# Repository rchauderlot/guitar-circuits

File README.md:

# Guitar Circuits

A place for my guitar-related circuits. 

For the moment, I just made some simple circuits to help me in the process of building guitar effects. But, my plans are add more complex circuits, like pedals, on board effects or, even, full amps, in the future.

All of the circuits in this repo are made using the freeware version of the [EAGLE CAD software](http://www.cadsoftusa.com/), which is cross-platform and has no cost for a hobbyist use. You could download it from the [EAGLE download page](http://www.cadsoftusa.com/download-eagle/)

To configure EAGLE I just add the paths of where the repo is cloned to the project and libraries directories in the *Options* > *Directories* menu. Remember, directories are colon separated in EAGLE. A configuration sample is (it is my current configuration ;-) ):

Libraries:
<pre><code>
$EAGLEDIR/lbr:$HOME/Documents/circuits/guitar-circuits/libs/
</pre></code>

Projects:
<pre><code>
$HOME/Documents/circuits:$EAGLEDIR/projects/examples
</pre></code>

## Circuits

### gm-lbr
This is not a circuit it is a library got form [Gaussmarkov website](http://gaussmarkov.net/) (very cool site, check it out). I’m using it because it is oriented to create pedals and fits my needs very well. It is free, but, all the copyrights belongs to Gaussmarkov as he says in his [About page](http://gaussmarkov.net/wordpress/about/).

### true-bypass
This is a tiny board intended to be attached to a heavy duty foot switch and where you connect all the parts of the circuit (effect board, jacks, led, battery clip and power supply). I made it to avoid to have a mess of wires inside of the pedal case. It is a single sided board, and it is very easy to develop at home.

### true-bypass-2.0
This board is based on the previous one but adds the feature of disconect the power supply when the output jack is unpluged. A stereo jack at the output is needed to take that advantadge.

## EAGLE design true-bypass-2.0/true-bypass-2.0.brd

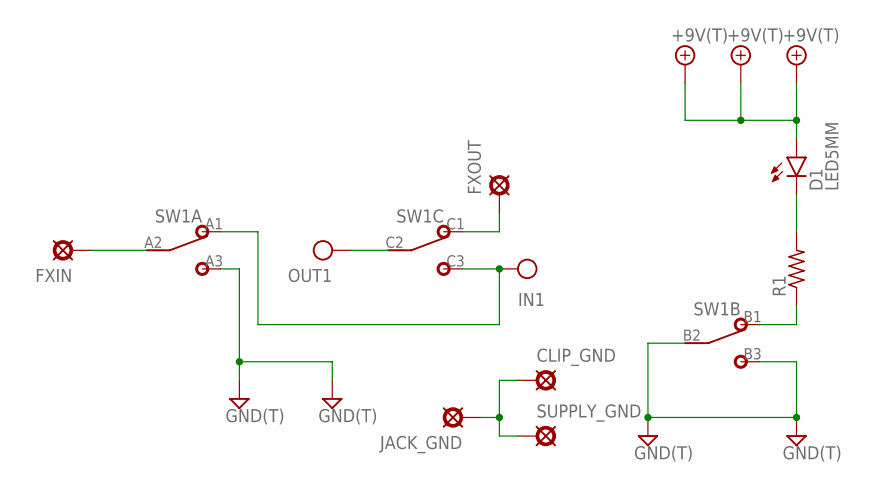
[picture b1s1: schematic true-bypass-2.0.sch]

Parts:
+9V1, +9V2, +9V3: +9V(T); SQUARE
CLIP_GND: PAD; SQUARE
D1: LED5MM
FXIN: PAD; SQUARE
FXOUT: PAD; SQUARE
GND1, GND3, GND4, GND5: GND(T); SQUARE
IN1: IN(T); SQUARE
JACK_GND: PAD; SQUARE
OUT1: OUT(T); SQUARE
R1: 6MM.3; R0207/3
SUPPLY_GND: PAD; SQUARE
SW1: 3PDTBLUE; CHINABLUE

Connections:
+9V: +9V1.1, +9V2.1, +9V3.1, D1.A
GND: GND1.1, GND3.1, GND4.1, GND5.1, SW1.A3 (3), SW1.B2 (2), SW1.B3 (3)
IN: IN1.1, SW1.A1 (1), SW1.C3 (3)
unnamed: FXIN.1, SW1.A2 (2)
unnamed: D1.K (C), R1.2
unnamed: R1.1, SW1.B1 (1)
unnamed: FXOUT.1, SW1.C1 (1)
unnamed: CLIP_GND.1, JACK_GND.1, SUPPLY_GND.1
OUT: OUT1.1, SW1.C2 (2)

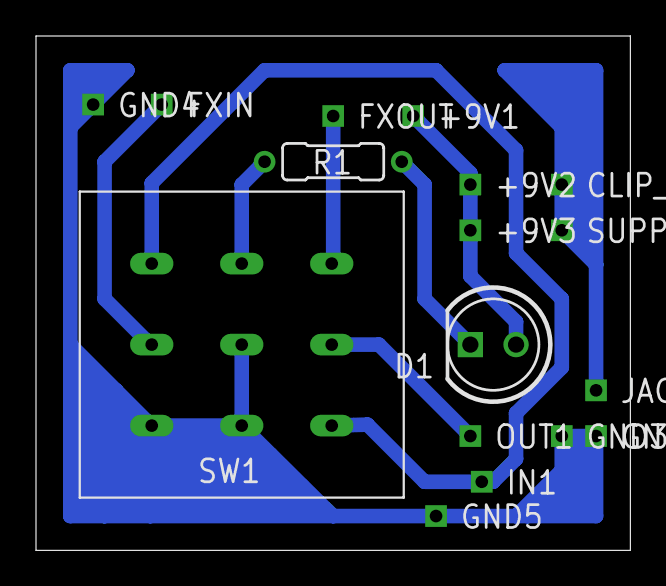
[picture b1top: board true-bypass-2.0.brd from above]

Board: 2 copper layers, 33.0 x 28.6 mm, 17 parts (0 on the bottom side), 9 nets.

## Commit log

2015-08-20 Upload gaussmarkov library.
2015-08-20 Upload the true-bypass board.
2015-08-20 Readme file updated.
2015-08-20 Fixed some strange characters in the Readme file.
2015-08-20 Fixed more strange characters from the Readme file.
2015-08-20 Added the true-bypass eagle configurarition.
2015-08-20 Added the first version of the true-bypass-2.0 circuit. It sill need some polish.
2015-08-20 Track gitignore file.
